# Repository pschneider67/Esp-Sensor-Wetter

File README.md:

# Platine KiCad Projekt - Esp-Sensor-Wetter

Die Platine kann z.B. als EspHome Senorplatine eingesetzt werden.
Ein Betrieb mit 3 AA Baterien ist möglich.

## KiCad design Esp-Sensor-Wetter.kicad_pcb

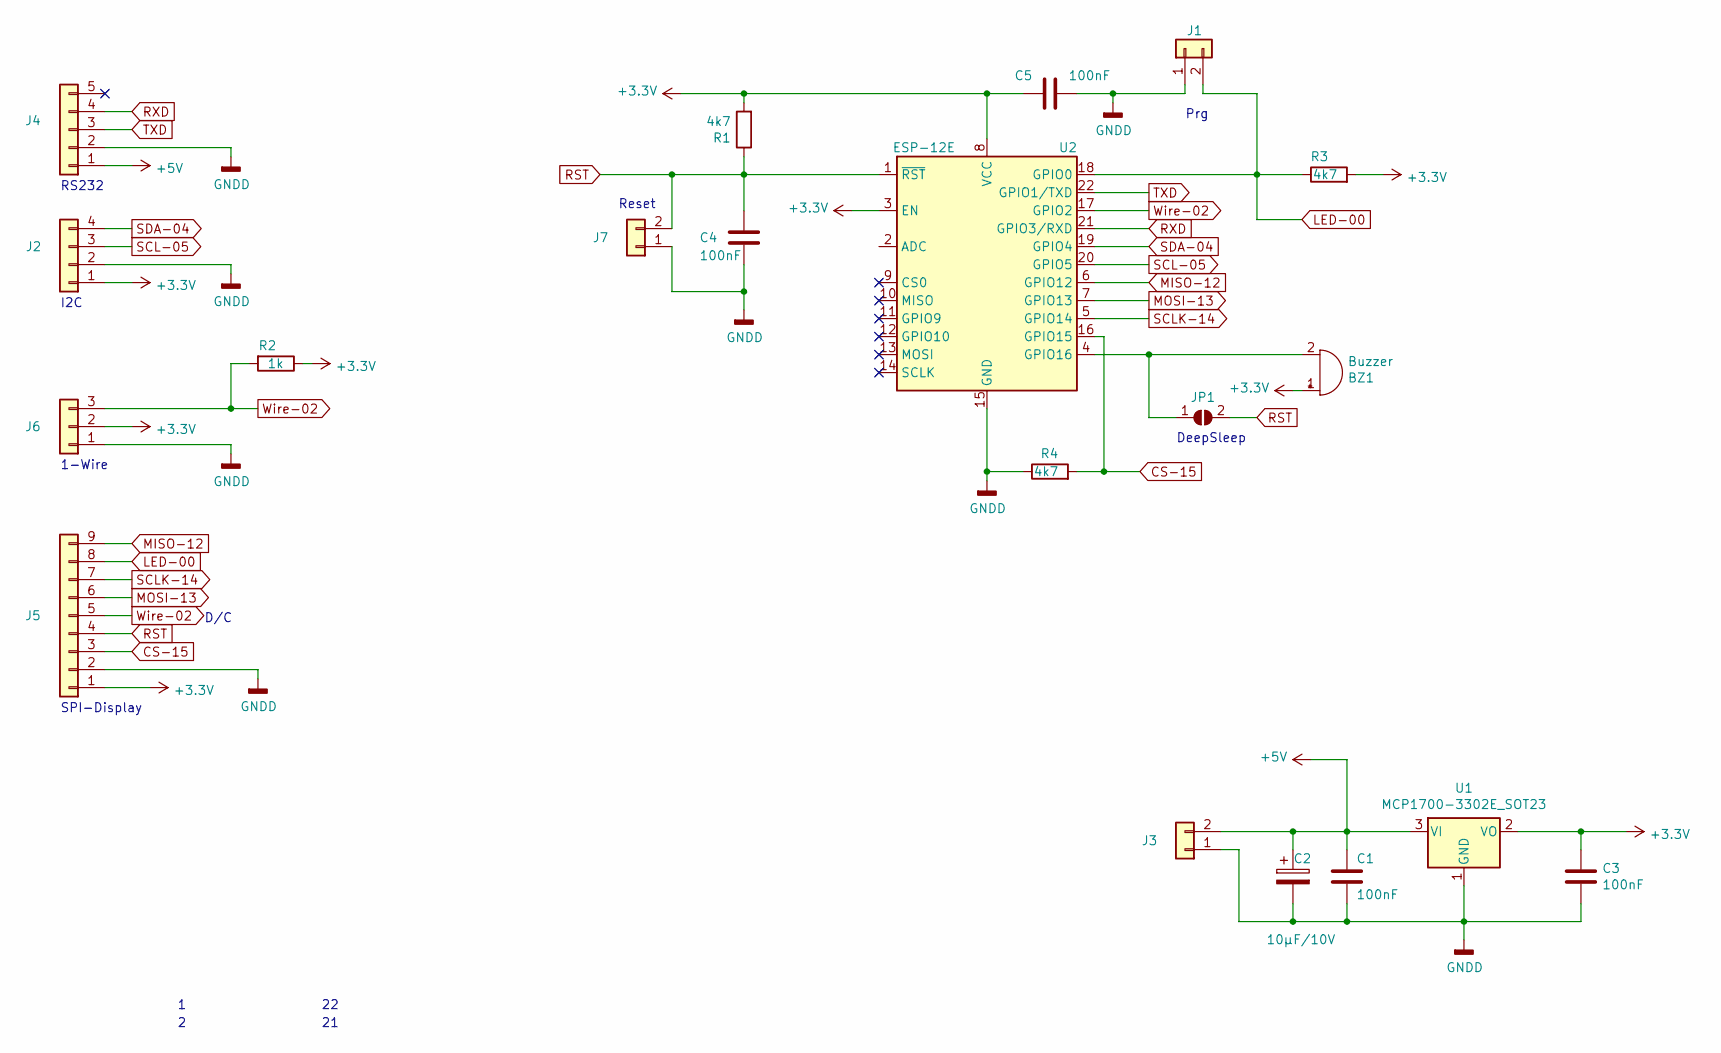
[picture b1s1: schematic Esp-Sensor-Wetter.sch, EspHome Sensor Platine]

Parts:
BZ1: Buzzer; Buzzer_9x5RM5
C1, C3, C4, C5: 100nF; C_1206_3216Metric_Pad1.33x1.80mm_HandSolder
C2: 10µF/10V; CP_Elec_5x5.3
J1, J3, J7: Conn_01x02; PinHeader_1x02_P2.54mm_Vertical
J2: Conn_01x04; PinHeader_1x04_P2.54mm_Vertical
J4: Conn_01x05; PinHeader_1x05_P2.54mm_Vertical
J5: Conn_01x09; PinHeader_1x09_P2.54mm_Vertical
J6: Conn_01x03; PinHeader_1x03_P2.54mm_Vertical
JP1: SolderJumper_2_Open; SolderJumper-2_P1.3mm_Open_RoundedPad1.0x1.5mm
R1, R3, R4: 4k7; R_1206_3216Metric_Pad1.30x1.75mm_HandSolder
R2: 1k; R_1206_3216Metric_Pad1.30x1.75mm_HandSolder
U1: MCP1700-3302E_SOT23; SOT-23
U2: ESP-12E

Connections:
+3V3: BZ1.1 (-), C3.1, C5.2, J2.1, J5.1, J6.2, R1.2, R2.1, R3.2, U1.2 (VO), U2.3 (EN), U2.8 (VCC)
+5V: C1.1, C2.1, J3.2, J4.1, U1.3 (VI)
CS-15: J5.3, R4.2, U2.16 (GPIO15)
GNDD: C1.2, C2.2, C3.2, C4.2, C5.1, J1.1, J2.2, J3.1, J4.2, J5.2, J6.1, J7.1, R4.1, U1.1 (GND), U2.15 (GND)
LED-00: J1.2, J5.8, R3.1, U2.18 (GPIO0)
MISO-12: J5.9, U2.6 (GPIO12)
MOSI-13: J5.6, U2.7 (GPIO13)
unnamed: BZ1.2 (+), JP1.1 (A), U2.4 (GPIO16)
RST: C4.1, J5.4, J7.2, JP1.2 (B), R1.1, U2.1 (~RST)
RXD: J4.4, U2.21 (GPIO3/RXD)
SCL-05: J2.3, U2.20 (GPIO5)
SCLK-14: J5.7, U2.5 (GPIO14)
SDA-04: J2.4, U2.19 (GPIO4)
TXD: J4.3, U2.22 (GPIO1/TXD)
Wire-02: J5.5, J6.3, R2.2, U2.17 (GPIO2)

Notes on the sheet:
RS232
Reset
Prg
I2C
1-Wire
DeepSleep
SPI-Display
D/C

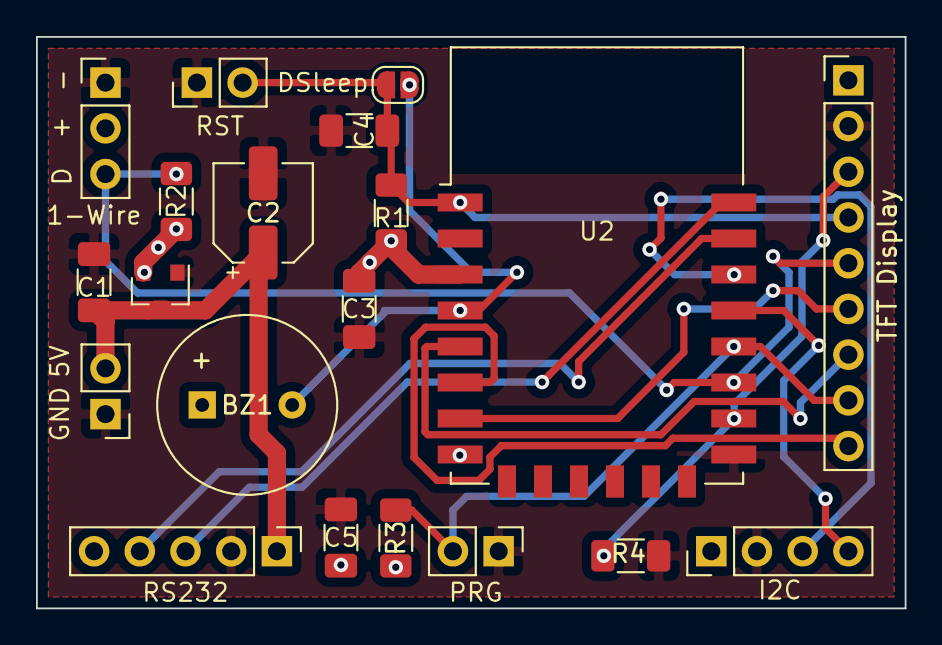
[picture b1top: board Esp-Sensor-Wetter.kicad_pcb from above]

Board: 2 copper layers, 48.3 x 31.8 mm, 20 parts (0 on the bottom side), 15 nets.

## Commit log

2021-11-04 Start Esp-Sensor-Wetter
